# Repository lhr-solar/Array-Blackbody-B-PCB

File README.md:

# Array-StandaloneIrradiancePCB
Standalone irradiance board for testing PV's photovoltaics with the IV curve tracer

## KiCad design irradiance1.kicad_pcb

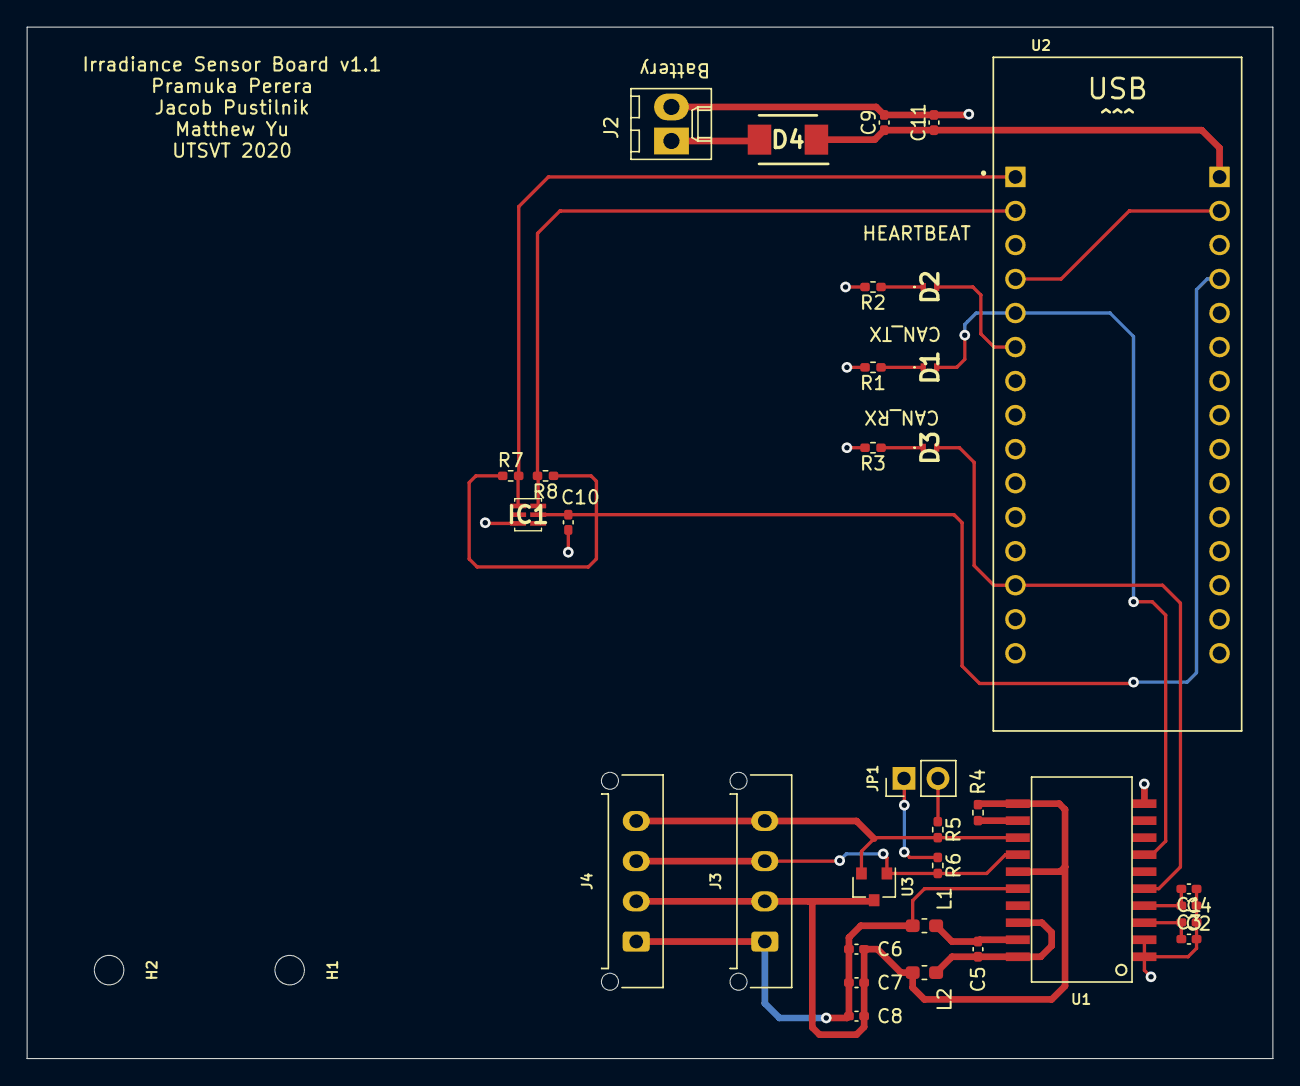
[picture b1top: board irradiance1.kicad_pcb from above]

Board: 2 copper layers, 93.0 x 77.0 mm, 35 parts (0 on the bottom side), 23 nets.

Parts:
C1, C6, C11: 10u; C_0402_1005Metric_Pad0.74x0.62mm_HandSolder
C2, C3, C4, C7, C9: 0.1u; C_0402_1005Metric_Pad0.74x0.62mm_HandSolder
C5: 0.22u; C_0402_1005Metric_Pad0.74x0.62mm_HandSolder
C8: 0.01u; C_0402_1005Metric_Pad0.74x0.62mm_HandSolder
C10: 1u; C_0402_1005Metric_Pad0.74x0.62mm_HandSolder
D1: CAN_TX; SM0402GC
D2: HEARTBEAT; SM0402GC
D3: CAN_RX; SM0402GC
D4: D_Schottky; SODFL5436X110N
H1, H2: MountingHole; MountingHole_2.2mm_M2
IC1: TSL25911FN
J2: Battery; Molex_KK-6410-02_02x2.54mm_Straight
J3: CAN_In; Molex_Micro-Fit_3.0_43650-0415_1x04_P3.00mm_Vertical
J4: CAN_Out; Molex_Micro-Fit_3.0_43650-0415_1x04_P3.00mm_Vertical
JP1: Termination Resistors; PinHeader_1x02_P2.54mm_Vertical
L1, L2: 2k; L_0603_1608Metric_Pad1.05x0.95mm_HandSolder
R1, R2, R3: 330; R_0402_1005Metric_Pad0.72x0.64mm_HandSolder
R4: 0; R_0402_1005Metric_Pad0.72x0.64mm_HandSolder
R5, R6: 60; R_0402_1005Metric_Pad0.72x0.64mm_HandSolder
R7, R8: 1.5k; R_0402_1005Metric_Pad0.72x0.64mm_HandSolder
U1: ADM3055E; ADM3055EBRIZ
U2: Nucleo_L432KC; MODULE_NUCLEO-L432KC
U3: CDSOT23-T24CAN; SOT-23

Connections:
+3V3: C3.1, C4.1, U1.4 (V_IO)
+5V: C1.1, C2.1, U1.3 (V_In)
+9VA: C9.1, C11.1, D4.1 (K), U2.30 (VIN)
CAN_Rx: D3.2 (A), U1.5 (RX), U2.13 (D10)
CAN_Tx: D1.2 (A), U1.7 (TX), U2.5 (D2)
GND: C1.2, C2.2, C3.2, C4.2, C9.2, C10.1, C11.2, IC1.3 (GND), J2.2, R1.2, R2.2, R3.2, U1.1 (GND_In), U1.2 (GND_In), U1.10 (GND_In), U2.4 (GND), U2.29 (GND)
I2C_SCL: IC1.1 (SCL), R7.2, U2.1 (D1)
I2C_SDA: IC1.6 (SDA), R8.2, U2.2 (D0)
unnamed: C5.1, L1.2, U1.19 (V_ISO_Out)
unnamed: C5.2, L2.2, U1.18 (GND_ISO_Out), U1.20 (GND_ISO_Out)
unnamed: C6.1, C7.1, C8.1, J3.1 (5V), J4.1 (5V), L1.1, U1.16 (V_ISO_In)
unnamed: C6.2, C7.2, C8.2, J3.2 (GND), J4.2 (GND), L2.1, R4.1, U1.11 (GND_ISO_In), U1.15 (GND_ISO_In), U3.3 (GND)
unnamed: D1.1 (K), R1.1
unnamed: D2.1 (K), R2.1
unnamed: D2.2 (A), U2.6 (D3)
unnamed: D3.1 (K), R3.1
unnamed: D4.2 (A), J2.1
unnamed: J3.3 (CAN_H), J4.3 (CAN_H), R6.2, U1.14 (CAN_H), U3.1 (CAN_H)
unnamed: J3.4 (CAN_L), J4.4 (CAN_L), R5.2, U1.13 (CAN_L), U3.2 (CAN_L)
unnamed: JP1.1, R6.1
unnamed: JP1.2, R5.1
unnamed: R4.2, U1.12 (RS)
VDD: C10.2, IC1.5 (VDD), R7.1, R8.1, U2.27 (5V)

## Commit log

2021-01-17 First upload, all v1 schematics
    Includes the schematics for Eeschema and PCBNew and associated files
2021-02-13 Updated sheet details
2022-12-17 Initial commit of board revamp: - Reduced the size of the components to 0402s and 0603s to save space on the board - Modified the schematic to make it easier to look at and interpret - Added the TSL2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
2023-01-03 Made updates based on feedback: - Added series schottky diode for reverse polarity protection at J2 - Added cap and open-drain resistors for light sensor (IC1) - Connected grounds on Nucleo - Added 1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
